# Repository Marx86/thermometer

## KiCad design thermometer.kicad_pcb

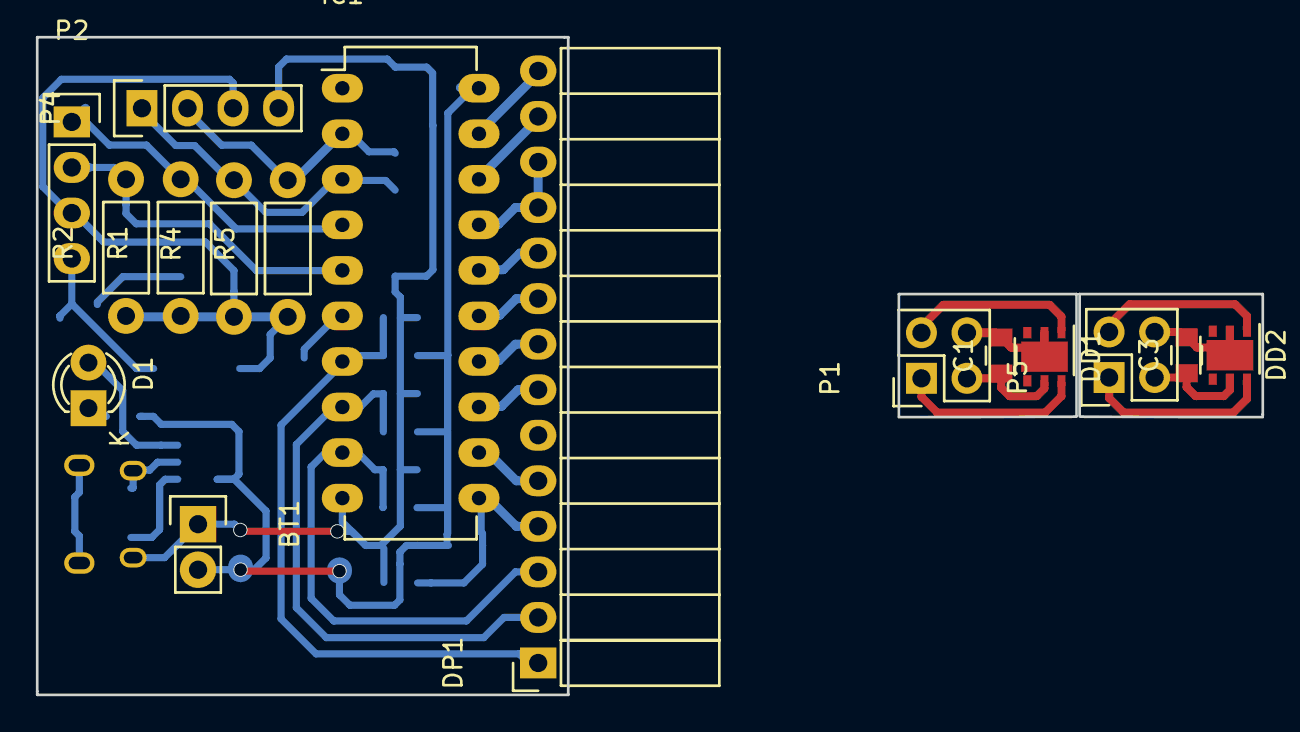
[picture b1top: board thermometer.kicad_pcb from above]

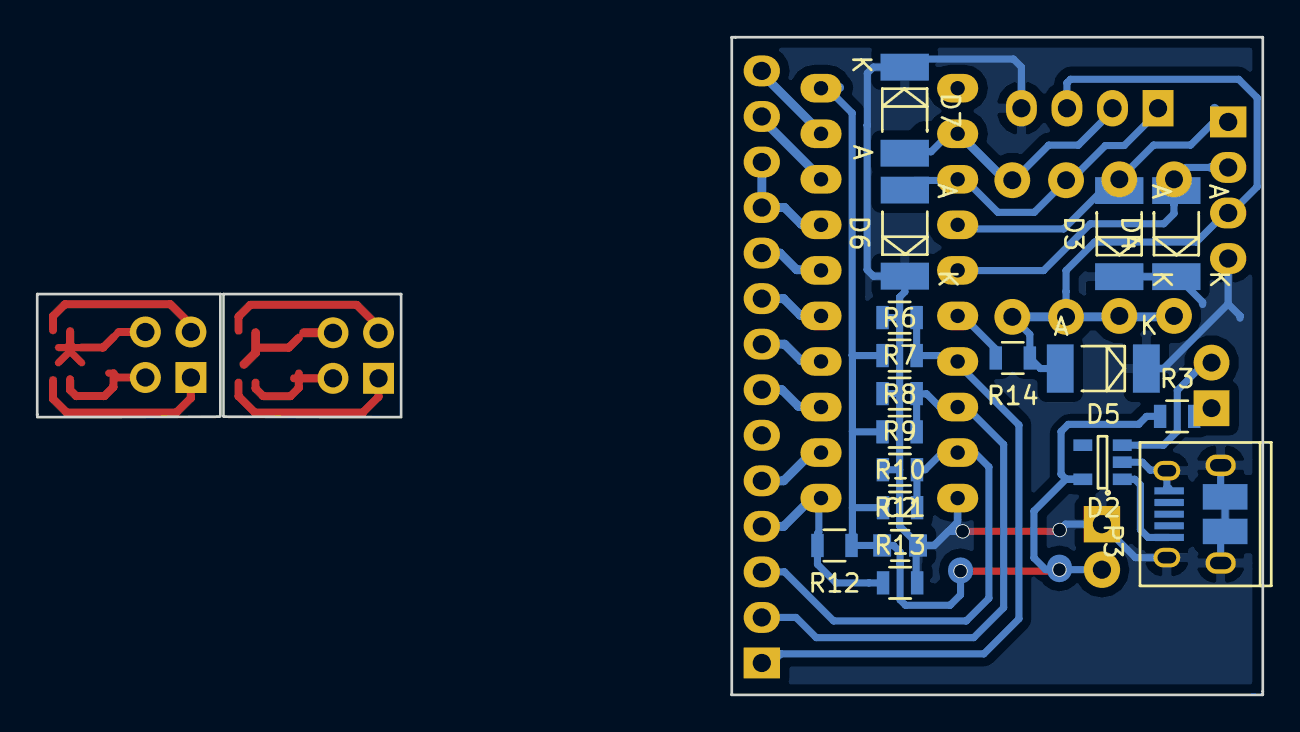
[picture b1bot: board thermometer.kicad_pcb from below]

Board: 2 copper layers, 68.4 x 36.7 mm, 34 parts (18 on the bottom side), 30 nets.

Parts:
BT1: BATTERY; Socket_Strip_Straight_1x02
C1, C2, C3: 0.1; C_0805
D1: LED; LED-3MM
D2: max1555; SOT-23-5
D3, D4, D5, D6, D7: 3.3v; MELF_Standard
DD1, DD2: Si705x; DFN-6-1EP_3x3mm_Pitch0.95mm
DP1: LCD_Display_5; Socket_Strip_Angled_1x14
IC1: ATTINY2313A-P; DIP-20_W7.62mm_LongPads
P1, P5: CONN_4; Pin_Header_Straight_2x02
P2, P4: CONN_4; Pin_Header_Straight_1x04
P3: CONN_6; USB_Micro-B_10103594-0001LF
R1, R2, R4, R5: 10k; Resistor_Horizontal_RM7mm
R3: 330; R_0805
R6, R7, R8, R9, R10, R11, R12, R13: 1M; R_0805
R14: 100; R_0805

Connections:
GND: C1.2, C3.2, DD1.2, DD1.7, DD2.2, DD2.7, P1.4, P5.4
GNDPWR: BT1.1, C2.2, D2.2, D3.1, D4.1, D5.1, D6.1, D7.1, IC1.10, P2.4, P3.5, P3.6, P4.4, R7.2, R9.2, R11.2, R13.2
NC: DD1.3, DD1.4, DD2.3, DD2.4
unnamed: D1.1, R3.2
unnamed: D1.2, D2.3
unnamed: D2.1, P3.1
unnamed: D3.2, IC1.4, P2.1, R1.2
unnamed: D4.2, IC1.5, P2.2, R2.2
unnamed: D5.2, P2.3, P4.3, R1.1, R2.1, R4.1, R5.1, R14.1
unnamed: D6.2, IC1.3, P4.1, R4.2
unnamed: D7.2, IC1.2, P4.2, R5.2
unnamed: DD1.1, P1.2
unnamed: DD1.6, P1.1
unnamed: DD2.1, P5.2
unnamed: DD2.6, P5.1
unnamed: DP1.1, IC1.7, R6.2, R7.1
unnamed: DP1.2, IC1.8, R8.2, R9.1
unnamed: DP1.3, IC1.9, R10.2, R11.1
unnamed: DP1.4, IC1.11, R12.2, R13.1
unnamed: DP1.5, IC1.12
unnamed: DP1.7, IC1.13
unnamed: DP1.8, IC1.14
unnamed: DP1.9, IC1.15
unnamed: DP1.10, IC1.16
unnamed: DP1.11, DP1.12, IC1.17
unnamed: DP1.13, IC1.18
unnamed: DP1.14, IC1.19
unnamed: IC1.6, R14.2
VCC: C1.1, C3.1, DD1.5, DD2.5, P1.3, P5.3
VDD: BT1.2, C2.1, D2.5, IC1.20, R3.1, R6.1, R8.1, R10.1, R12.1

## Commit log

2016-09-22 Init
2016-09-23 Add C src
2016-09-28 Add I2C functions
2016-09-29 Optimize C code
2016-09-30 Refactoring
2016-10-03 Add ltc1517
2016-10-03 Fix powersaving
2016-12-05 Fix Display
2016-12-05 Fix deg symbol
2016-12-09 Add power supply for temperature sensor.
2016-12-16 Add Makefile
2020-12-22 Fixes
